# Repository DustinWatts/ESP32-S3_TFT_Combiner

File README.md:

# ESP32-S3-DevKitC-1 + Touchscreen Combiner PCB

A PCB making it easy to combine an ESP32-S3-DevKitC-1 and an ILI9488 TFT + XPT2046 Touchsceen. ***One big adavantage of the ESP32-S3 is that is has USB HID support. So you can use the extra USB port on the DevKitC to connect to your computer, so you can use a USB Keyboard instead of BLE!*** FreeTouchDeck already support this.

## Order directly from PCBWay

You can order the PCB's directly from PCBWay here: [Order PCBs from PCBWay](https://www.pcbway.com/project/shareproject/ESP32_S3_TFT_Combiner_V1_92bd8d61.html "Order the combiner board directly from PCBWay")

## Download Gebers and use your own fab house

If you want to use your own fab house, you can find the gerbers (as wel as a .zip file for easy upload) in the [Gerber folder](/Gerbers "Download the gerbers") in this repo.

## The PCB

The PCB is designed in KiCad and uses 22-pin double row headers for the ESP32-S3 so you can use the GPIO's not used by the screen. It also uses a 14-pin header for the screen and a 4-pin header for the SD card. I recommend using female headers so you can remove both the ESP32-S3 and the screen.

Pins used by the screen, touchcontroller and SD card are:

| ESP32-S3 | Function |
|---|---|
| GPIO4  | SD_SELECT  |
| GPIO5  | TFT_RESET  |
| GPIO6  | TFT_DC_RS  |
| GPIO7  | TFT_BACKLIGHT  |
| GPIO10  | TFT_SELECT  |
| GPIO11  | MOSI  |
| GPIO12  | SCK  |
| GPIO13  | MISO  |
| GPIO15  | TOUCH_SELECT  |
| GPIO16  | TOUCH_IRQ  |

And off course 3V3 and GND are connected to the screen. 

The rest of the pins you can freely use. Use the ESP32-S3-DevKitC-1 pinout card as a reference: [Pinout Card on espressif.com](https://docs.espressif.com/projects/esp-idf/en/latest/esp32s3/hw-reference/esp32s3/user-guide-devkitc-1.html#pin-layout "ESP32-S3-DevKitC-1 Pinout Card")

## The ESP32-S3

The ESP32-S3 for this board is the ESP32-S3-DevKitC-1. Which is currently sold by:
- [Mouser](https://www.mouser.com/c/?q=ESP32-S3-DevKitC-1 "ESP32-S3-DevKitC-1 on Mouser")
- [DigiKey](https://www.digikey.nl/en/products/filter/rf-evaluation-and-development-kits-boards/859?s=N4IgTCBcDaIKIGUAKBmMBaBL0BECmAbgNICWALgMLoCMIAugL5A "ESP32-S3-DevKitC-1 on DigiKey")
- [Adafruit](https://www.adafruit.com/?q=ESP32-S3-DevKitC-1&sort=BestMatch "ESP32-S3-DevKitC-1 on Adafruit")
- [MakerFabs](https://www.makerfabs.com/search.html?&search=ESP32-S3-DevKitC-1 "ESP32-S3-DevKitC-1 on MakerFabs")

## The Touchsceen

The touchscreen used with this board is a 3.5" ILI9488 TFT with XPT2046 touchcontroller. You can find the screen here: 

- [AliExpress](https://s.click.aliexpress.com/e/_AMAa6B "Buy the ILI9488 with Touch on AliExpress") *
- [Amazon](https://amzn.to/3z2bf3f "Buy the ILI9488 with Touch on AliExpress") *

_* Afilliate link_

***Note: When you but the ILI9488 make sure you select the option "With Touch" if you have the possibility to do so!***

## The User_Setup.h

The User_Setup.h file in the folder with the same name is the User_Setup.h file you need to use the combiner PCB with the [TFT_eSPI](https://github.com/Bodmer/TFT_eSPI "TFT_eSPI lbrary by Bodmer") lbrary by Bodmer. Overwrite the contents of the original file and TFT_eSPI is now configured for use with the combiner board.

## FreeTouchDeck

FreeTouchDeck is currently being updated so it also supports the ESP32-S3. This also includes support for using the ESP32-S3 USB Keyboard HID. You can find the latest version here: https://github.com/DustinWatts/FreeTouchDeck. The updates are not in any release yet, you so you will have to download the source and compile it yourself. Hopefully this the next release will include ESP32-S3 support.

## The Case

The case was originally designed for the ESP32 + TFT combiner PCB and for use with FreeTouchDeck. But since the deminsions are the same, the case is also the same. You can find the .stl files to prin your own case in this repo in the folder called "3D Printable Case".

## Support Me

If you like what I am doing, there are a number of ways you can support me. 

| Platform | Link|
|:-----:|:-----|
|  | You can follow me on Twitter: [@dustinwattsnl](https://twitter.com/dustinwattsnl "Follow me on Twitter")|
|  | You can subscribe to my channel on Youtube: [/dustinWatts](https://www.youtube.com/dustinwatts "Subscribe to my YouTube channel") |
|  | You can support me by becoming a patron on Patreon: https://www.patreon.com/dustinwatts |
|  | You can make a one time donation using PayPal.me: https://www.paypal.me/dustinwattsnl |

## Get help

For quick acces to help you can join my Discord server: https://discord.gg/RE3XevS

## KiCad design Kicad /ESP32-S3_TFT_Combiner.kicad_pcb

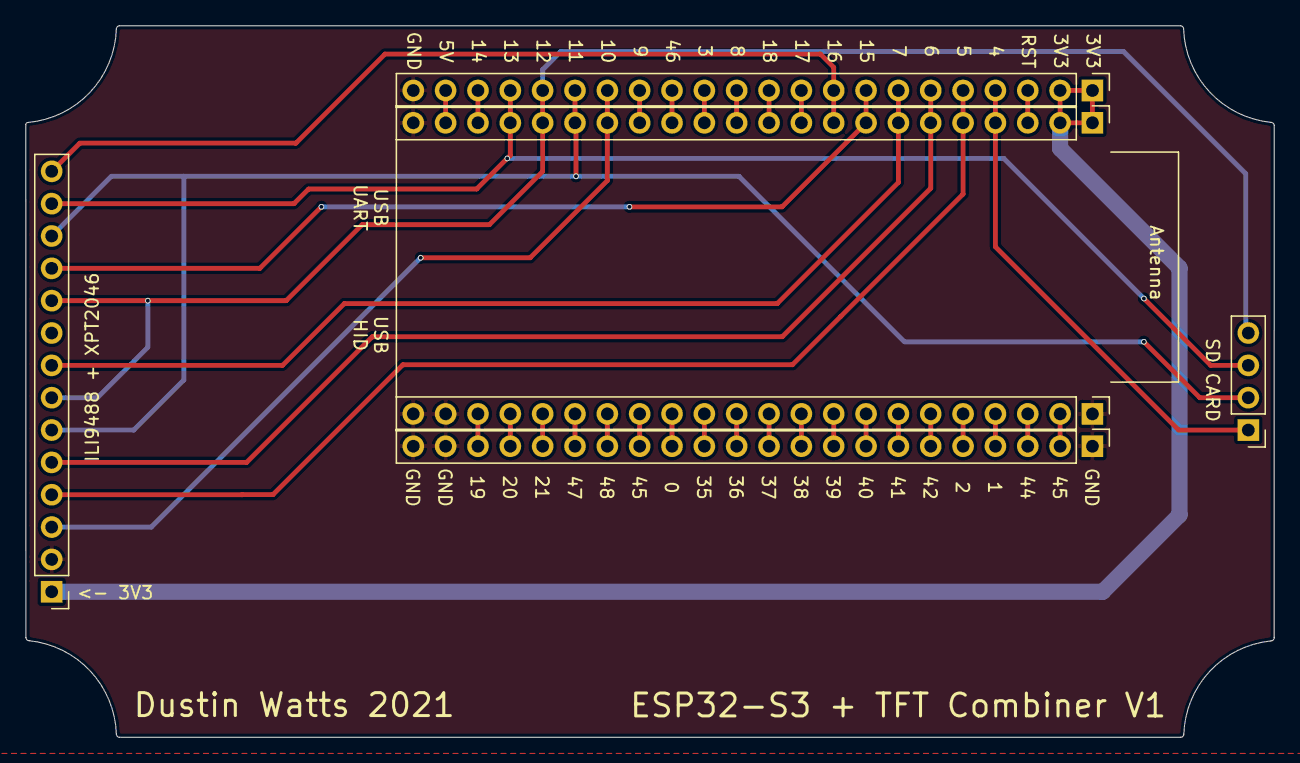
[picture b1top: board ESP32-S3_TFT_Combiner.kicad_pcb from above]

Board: 2 copper layers, 98.0 x 55.9 mm, 6 parts (0 on the bottom side), 40 nets.

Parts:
J1: Conn_01x04; PinHeader_1x04_P2.54mm_Vertical
J2: Conn_01x14; PinHeader_1x14_P2.54mm_Vertical
J3, J4, J5, J6: Conn_01x22; PinHeader_1x22_P2.54mm_Vertical

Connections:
+3V3: J2.1, J3.1, J3.2, J5.1, J5.2
+5V: J3.21, J5.21
GND: J2.2, J3.22, J4.1, J4.21, J4.22, J5.22, J6.1, J6.21, J6.22
GPIO0: J4.14, J6.14
GPIO1: J4.4, J6.4
GPIO2: J4.5, J6.5
GPIO3: J3.13, J5.13
GPIO8: J3.12, J5.12
GPIO9: J3.15, J5.15
GPIO14: J3.20, J5.20
GPIO17: J3.10, J5.10
GPIO18: J3.11, J5.11
GPIO19: J4.20, J6.20
GPIO20: J4.19, J6.19
GPIO21: J4.18, J6.18
GPIO35: J4.13, J6.13
GPIO36: J4.12, J6.12
GPIO37: J4.11, J6.11
GPIO38: J4.10, J6.10
GPIO39: J4.9, J6.9
GPIO40: J4.8, J6.8
GPIO41: J4.7, J6.7
GPIO42: J4.6, J6.6
GPIO43: J4.2, J6.2
GPIO44: J4.3, J6.3
GPIO45: J4.15, J6.15
GPIO46: J3.14, J5.14
GPIO47: J4.17, J6.17
GPIO48: J4.16, J6.16
MISO: J1.3, J2.13, J3.19, J5.19
MOSI: J1.2, J2.6, J2.12, J3.17, J5.17
RST: J3.3, J5.3
SCK: J1.4, J2.7, J2.10, J3.18, J5.18
SD_SELECT: J1.1, J3.4, J5.4
TFT_BACKLIGHT: J2.8, J3.7, J5.7
TFT_DC_RS: J2.5, J3.6, J5.6
TFT_RESET: J2.4, J3.5, J5.5
TFT_SELECT: J2.3, J3.16, J5.16
TOUCH_IRQ: J2.14, J3.9, J5.9
TOUCH_SELECT: J2.11, J3.8, J5.8

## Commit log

2022-05-17 Create LICENSE
2022-05-17 Added Kicad Project
    Kicad project, including .kicad_pcb, .net, .pro, and .sch
2022-05-17 Added schematic in PDF format
    Rev 1 schematic added.
2022-05-17 Updated Silkscreen
    Added pin numbering and correct a spelling mistake (XTP2040 = XPT2046)
2022-05-17 Added Gerbers
    Added gerber files and also a .zip file containing all the gerbers for easy upload.
2022-05-29 Update User_Setup.h
    Typo corrections.
2022-05-29 Clean up schematic
    Nothing has changed, just making it look nicer.
2022-05-29 Add 3D Printable Case
2022-05-29 Add images to assests
2022-05-30 Update images
2022-06-05 Rename files
    Replaced + by _
